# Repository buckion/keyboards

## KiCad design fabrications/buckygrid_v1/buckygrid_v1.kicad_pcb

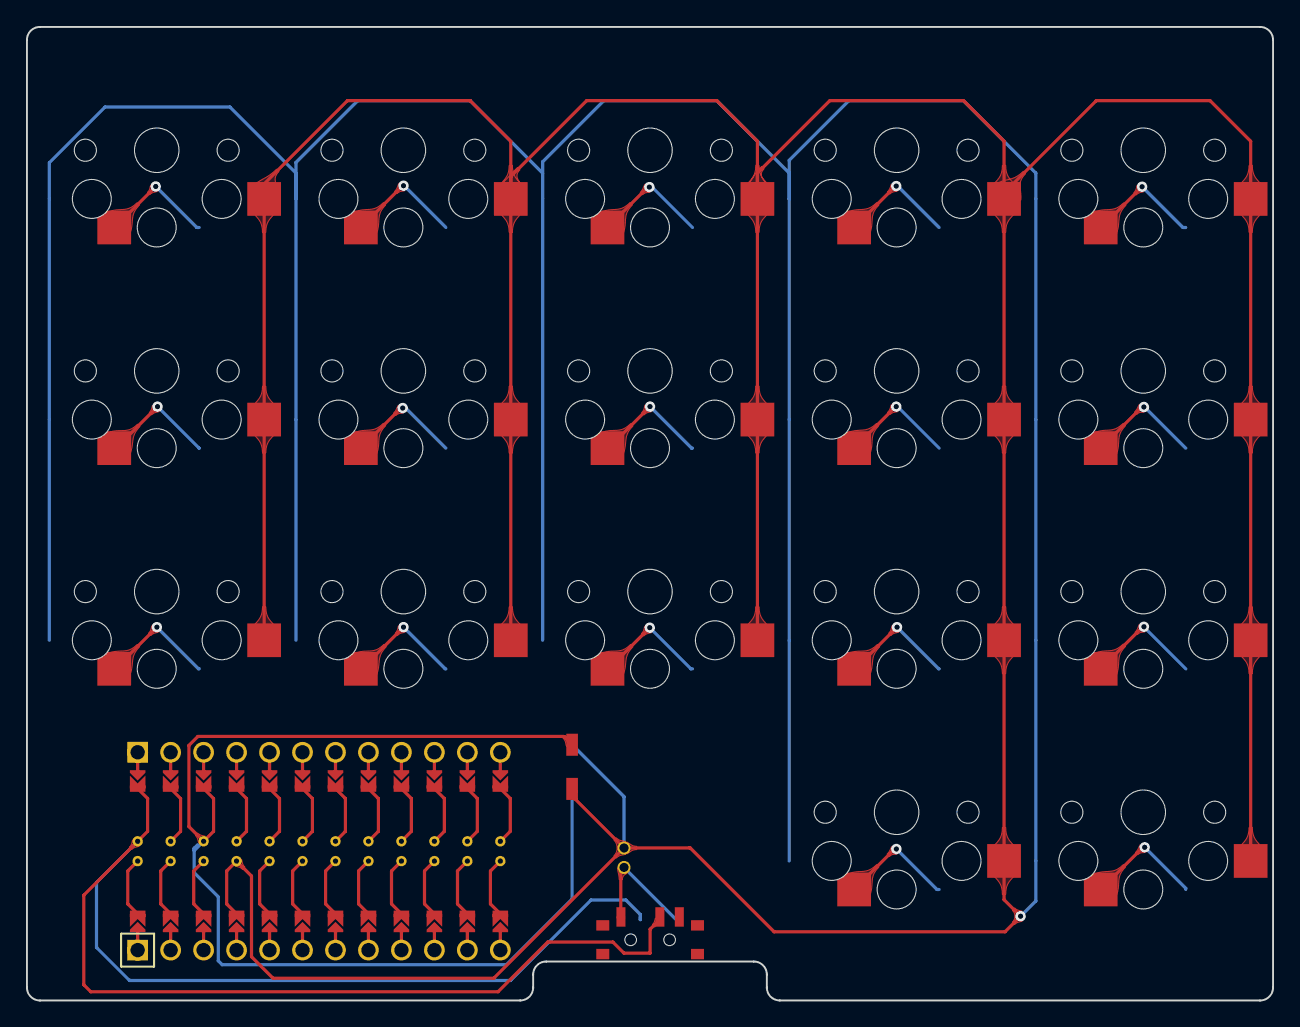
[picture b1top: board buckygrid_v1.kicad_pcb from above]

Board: 4 copper layers, 96.0 x 75.0 mm, 18 parts (0 on the bottom side), 18 nets.

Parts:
MCU1: ProMicro
S1, S2, S3, S4, S5, S6, S7, S8, S9, S10, S11, S12, S13, S14, S15, S16, S17: PG1350

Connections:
GND: MCU1.2, MCU1.21, MCU1.22, S1.2, S2.2, S3.2, S4.2, S5.2, S6.2, S7.2, S8.2, S9.2, S10.2, S11.2, S12.2, S13.2, S14.2, S15.2, S16.2, S17.2
grid_index_bottom: MCU1.16, S11.1
grid_index_home: MCU1.14, S12.1
grid_index_thumb: MCU1.18, S10.1
grid_index_top: MCU1.11, S13.1
grid_inner_bottom: MCU1.15, S15.1
grid_inner_home: MCU1.13, S16.1
grid_inner_thumb: MCU1.17, S14.1
grid_inner_top: MCU1.12, S17.1
grid_middle_bottom: MCU1.9, S7.1
grid_middle_home: MCU1.8, S8.1
grid_middle_top: MCU1.7, S9.1
grid_pinky_bottom: MCU1.23, S1.1
grid_pinky_home: MCU1.20, S2.1
grid_pinky_top: MCU1.24, S3.1
grid_ring_bottom: MCU1.6, S4.1
grid_ring_home: MCU1.19, S5.1
grid_ring_top: MCU1.5, S6.1

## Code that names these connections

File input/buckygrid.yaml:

points:
  key:
    padding: cy
    spread: cx
    rotate: 180
    footprints:
      choc_hotswap:
        type: choc
        params:
          hotswap: true
          reverse: true
        nets:
          from: =name
          to: GND
  zones:
    grid:
      rows:
        thumb:
        bottom:
        home:
        top:
      columns:
        pinky.rows.thumb.skip: true
        ring.rows.thumb.skip: true
        middle.rows.thumb.skip: true
        index:
        inner:
outlines:
  exports:
    raw:
      - type: keys
        side: left
        size: [cx + 2, cy + 2]
    thumb_row:
      - type: polygon
        points:
          - ref: grid_pinky_bottom
            shift: [0.5 cx + 1, 0]
          - ref: grid_pinky_bottom
            shift: [0.5 cx + 1, 1.5 cy + 6]
          - ref: grid_middle_bottom
            shift: [0.5 cx, 1.5 cy + 6]
          - ref: grid_middle_bottom
            shift: [0.5 cx, 1.5 cy + 3]
          - ref: grid_middle_bottom
            shift: [-0.5 cx, 1.5 cy + 3]
          - ref: grid_middle_bottom
            shift: [-0.5 cx, 1.5 cy + 6]
          - ref: grid_inner_bottom
            shift: [-0.5 cx - 1, 1.5 cy + 6]
          - ref: grid_inner_bottom
            shift: [-0.5 cx - 1, 0]
          - ref: grid_pinky_bottom
            shift: [0.5 cx + 1, 0]
    base_cutout:
      - type: outline
        name: raw
      - type: outline
        name: thumb_row
        operation: add
    cutout:
      - type: outline
        name: base_cutout
        fillet: 1 
    keycaps:
      - type: keys
        side: left
        size: [cx - 0.5, cy - 0.5]
        bound: false
    feet:
      - type: circle
        radius: 3
        anchor:
          ref: grid_pinky_top
          shift: [0.5 cx + 1 - 3, -0.5 cy - 1 + 3]
      - type: circle
        radius: 3
        anchor:
          ref: grid_pinky_bottom
          shift: [0.5 cx + 1 - 3, 1.5 cy + 6 - 3]
      - type: circle
        radius: 3
        anchor:
          ref: grid_inner_top
          shift: [-0.5 cx - 1 + 3, -0.5 cy - 1 + 3]
      - type: circle
        radius: 3
        anchor:
          ref: grid_inner_bottom
          shift: [-0.5 cx - 1 + 3, 1.5 cy + 6 - 3]
pcbs:
  buckygrid:
    outlines:
      board:
        outline: cutout
      keycaps:
        outline: keycaps
        layer: Eco1.User
      feet:
        outline: feet
        layer: Eco1.User
    footprints:
      nice_nano_socket:
        type: promicro_pretty
        # params:
        #   orientation: up
        anchor:
          ref: grid_pinky_bottom
          shift: [0.5 cx + 1 - 19.5 - 3 , 0.5 cy + 8.5 + 3]
          rotate: 180
        nets:
          P0: grid_pinky_bottom
          P2: grid_pinky_home
          P1: grid_pinky_top
          P20: grid_ring_bottom
          P3: grid_ring_home
          P21: grid_ring_top
          P15: grid_middle_bottom
          P18: grid_middle_home
          P19: grid_middle_top
          P4: grid_index_thumb
          P6: grid_index_bottom
          P8: grid_index_home
          P16: grid_index_top
          P5: grid_inner_thumb
          P7: grid_inner_bottom
          P9: grid_inner_home
          P10: grid_inner_top
      power_switch:
        type: pcm12
        params:
          reverse: true
        anchor:
          ref: grid_middle_bottom
          shift: [0, 1.5 cy + 3 - 1.8]
          rotate: 180
        nets:
          from: pos
          to: RAW
      reset_button:
        type: b3u1000p
        params:
          reverse: true
        anchor:
          ref: grid_middle_bottom
          shift: [0.5 cx - 3, 0.5 cy + 5]
          rotate: 270
        nets:
          r1: RST
          r2: GND
      battery_terminal:
        type: bat
        anchor:
          ref: grid_middle_bottom
          shift: [2, 1.5 cy - 5]
        nets: 
          neg: GND

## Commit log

2022-08-20 buckyboard v1
2022-09-04 Buckyboard v1 manufactured
2022-09-20 buckygrid v1 ready for routing
2022-09-21 fabrication ready buckygrid v1
